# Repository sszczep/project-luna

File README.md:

# project Luna

project Luna is an 81-key keyboard, featuring unconventional layout, per-key backlight and hotswap.

## Case renders

## Schematics

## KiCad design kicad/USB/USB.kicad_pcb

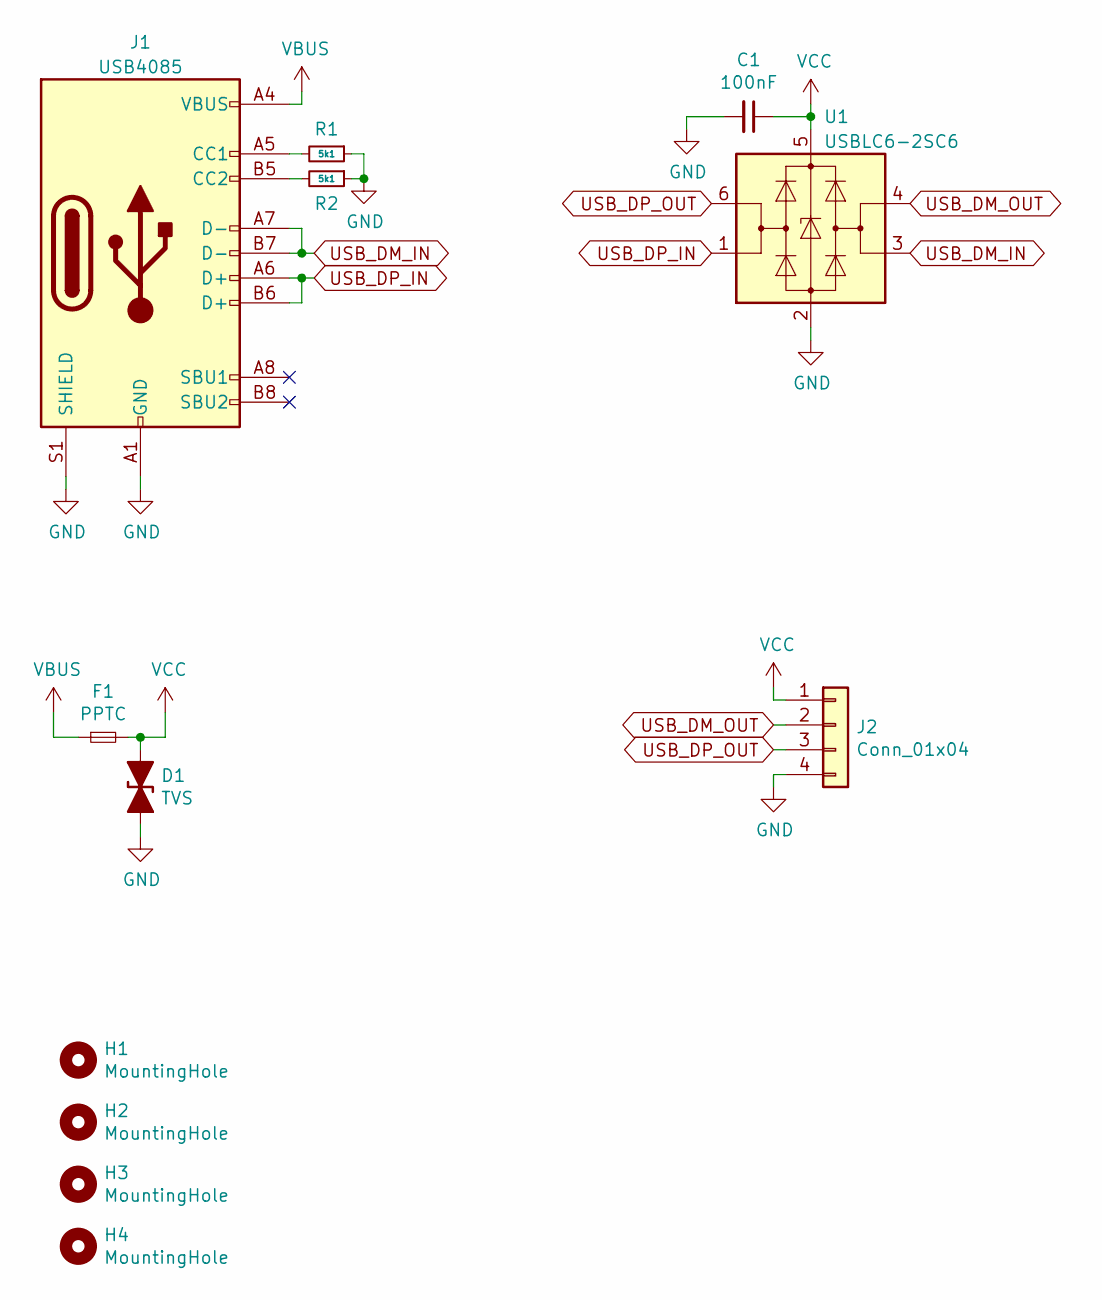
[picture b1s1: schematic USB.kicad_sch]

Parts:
C1: 100nF; C_0603_1608Metric_Pad1.08x0.95mm_HandSolder
D1: TVS; D_SMF
F1: PPTC; Fuse_0805_2012Metric_Pad1.15x1.40mm_HandSolder
H1, H2, H3, H4: MountingHole; MountingHole_2.2mm_M2_ISO7380
J1: USB4085; USB_C_Receptacle_GCT_USB4085
J2: Conn_01x04; JST_SH_SM04B-SRSS-TB_1x04-1MP_P1.00mm_Horizontal
R1, R2: 5k1; R_0603_1608Metric_Pad0.98x0.95mm_HandSolder
U1: USBLC6-2SC6; SOT-23-6_Handsoldering

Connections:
GND: C1.2, D1.2 (A2), J1.A1 (GND), J1.A12 (GND), J1.B1 (GND), J1.B12 (GND), J1.S1 (SHIELD), J2.4, R1.1, R2.1, U1.2 (GND)
unnamed: J1.A5 (CC1), R1.2
unnamed: J1.B5 (CC2), R2.2
USB_DM_IN: J1.A7 (D-), J1.B7 (D-), U1.3 (I/O2)
USB_DM_OUT: J2.2, U1.4 (I/O2)
USB_DP_IN: J1.A6 (D+), J1.B6 (D+), U1.1 (I/O1)
USB_DP_OUT: J2.3, U1.6 (I/O1)
VBUS: F1.1, J1.A4 (VBUS), J1.A9 (VBUS), J1.B4 (VBUS), J1.B9 (VBUS)
VCC: C1.1, D1.1 (A1), F1.2, J2.1, U1.5 (VBUS)

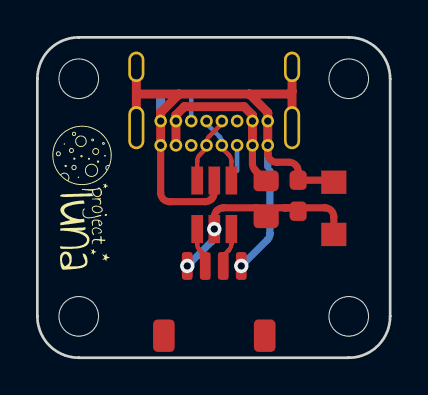
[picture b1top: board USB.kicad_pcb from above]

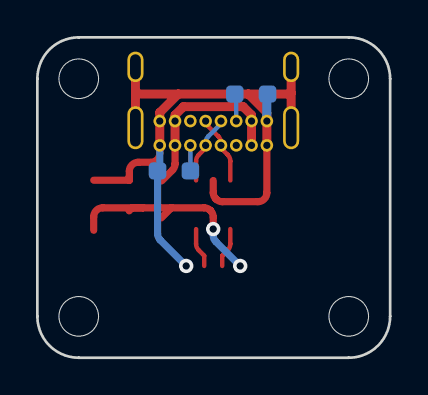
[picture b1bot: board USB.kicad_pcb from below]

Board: 2 copper layers, 19.6 x 17.8 mm, 12 parts (2 on the bottom side), 9 nets.

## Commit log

2022-03-27 Remove .DS_Store files
2022-03-27 Remove Release folder
